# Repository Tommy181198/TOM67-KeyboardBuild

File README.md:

# TOM67-KeyboardBuild
 My First ever keyboard build

 MCU Schemantics:

 The rest of the Schemantics :

The Matrix :

The PCB Component placement before routing

Switch Matrix Routing (its a mess):

Crystal Route:

USB TYPE C Power Routing (I know its a mess) :

Finished Route

3D Render :

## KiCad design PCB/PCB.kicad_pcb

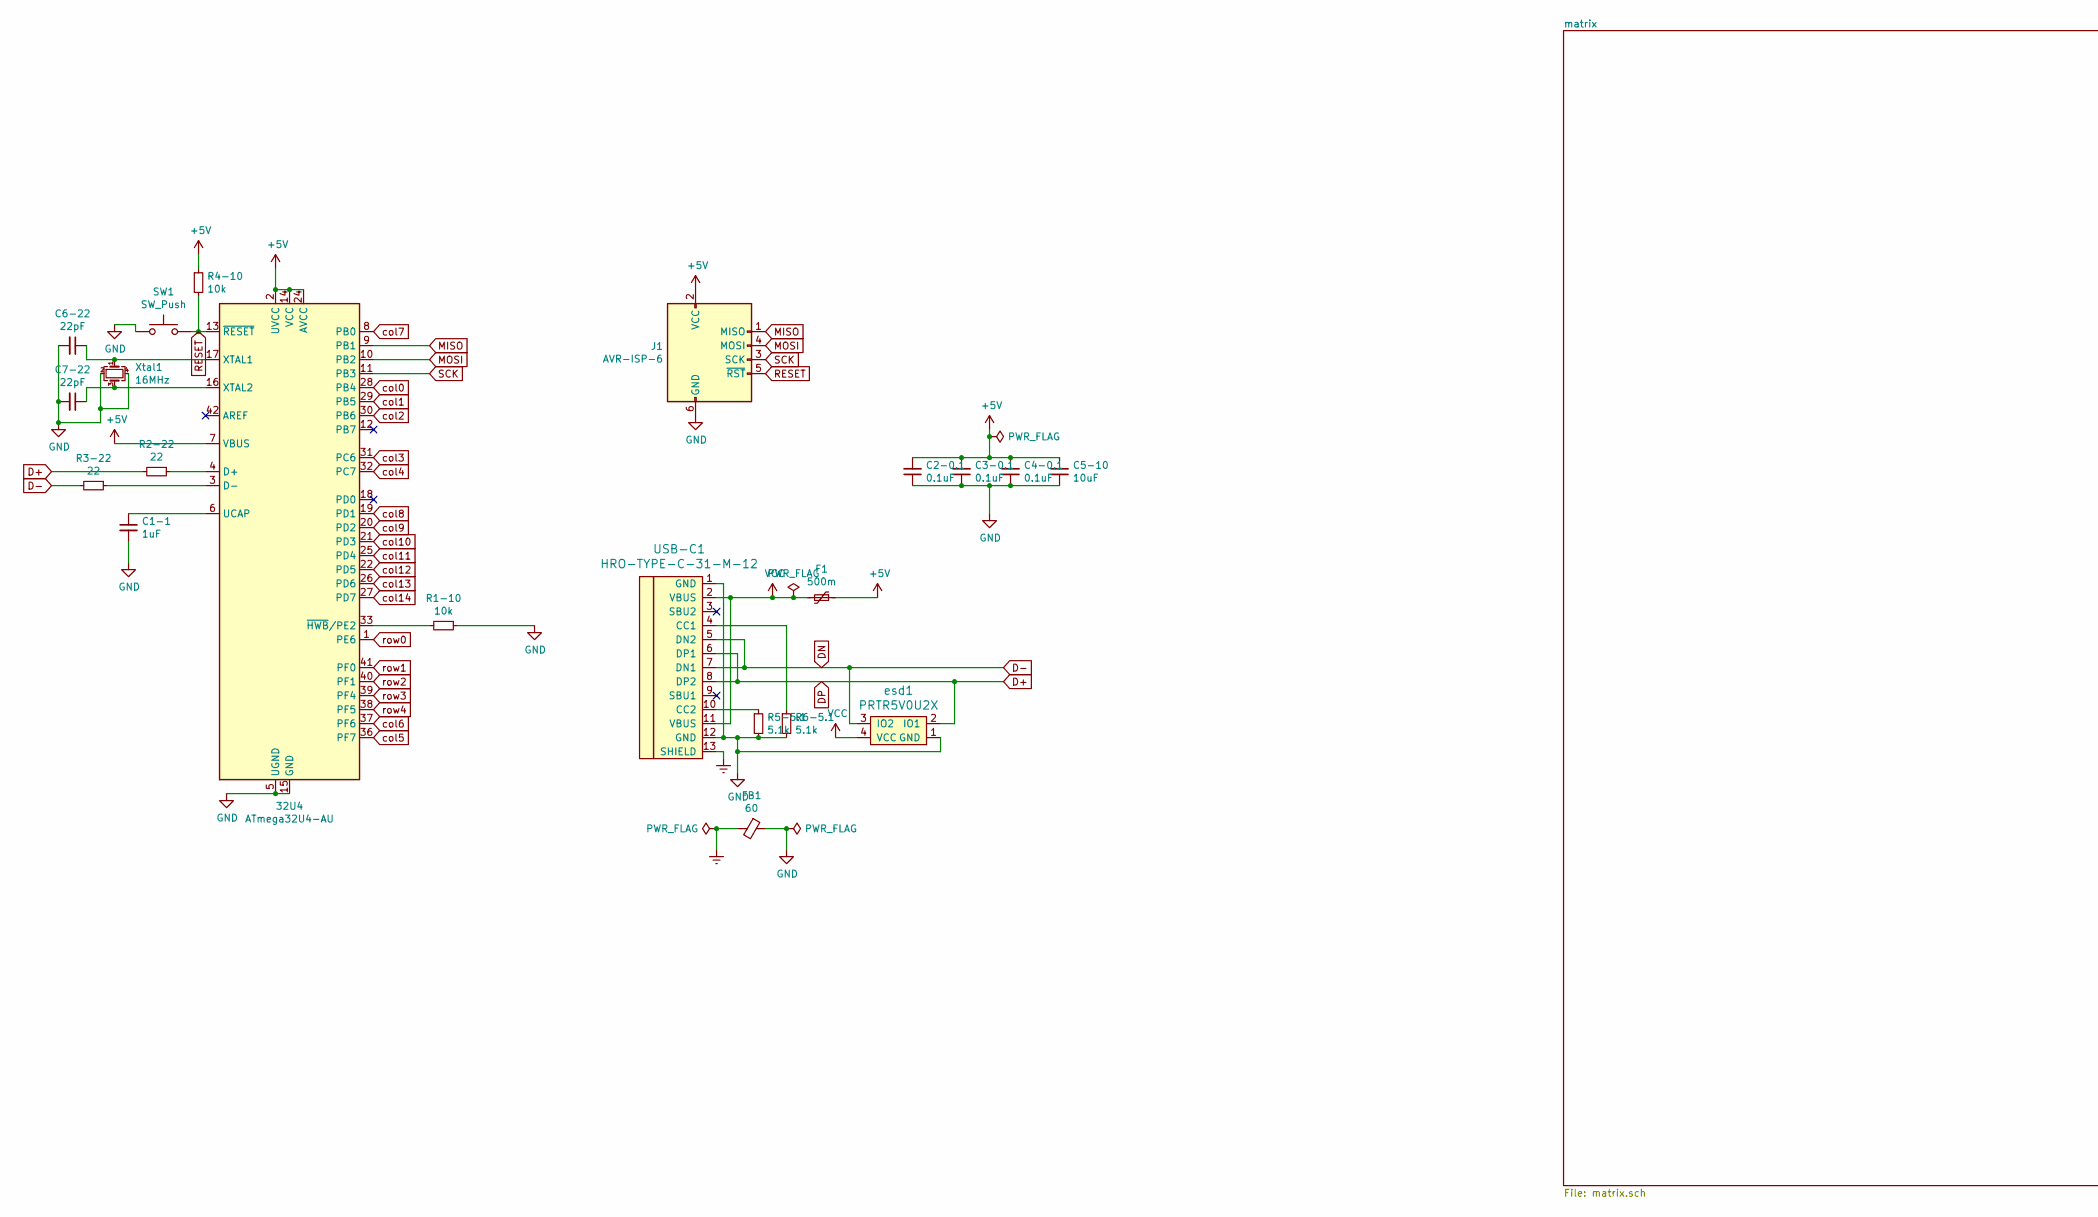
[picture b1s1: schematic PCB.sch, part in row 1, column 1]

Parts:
32U4: ATmega32U4-AU; TQFP-44_10x10mm_P0.8mm
C1-1: 1uF; C_0805_2012Metric_Pad1.18x1.45mm_HandSolder
C2-0.1, C3-0.1, C4-0.1: 0.1uF; C_0805_2012Metric_Pad1.18x1.45mm_HandSolder
C5-10: 10uF; C_0805_2012Metric_Pad1.18x1.45mm_HandSolder
C6-22, C7-22: 22pF; C_0805_2012Metric_Pad1.18x1.45mm_HandSolder
F1: 500m; Fuse_1206_3216Metric_Pad1.42x1.75mm_HandSolder
FB1: 60; L_0805_2012Metric_Pad1.05x1.20mm_HandSolder
J1: AVR-ISP-6; Reset_Pretty
R1-10, R4-10: 10k; R_0805_2012Metric_Pad1.20x1.40mm_HandSolder
R2-22, R3-22: 22; R_0805_2012Metric_Pad1.20x1.40mm_HandSolder
R5-5.1, R6-5.1: 5.1k; R_0805_2012Metric_Pad1.20x1.40mm_HandSolder
SW1: SW_Push; SW_SPST_TL3342
USB-C1: HRO-TYPE-C-31-M-12; HRO-TYPE-C-31-M-12-HandSoldering
Xtal1: 16MHz; Crystal_SMD_3225-4Pin_3.2x2.5mm
esd1: PRTR5V0U2X; SOT143B

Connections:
+5V: 32U4.2 (UVCC), 32U4.7 (VBUS), 32U4.14 (VCC), 32U4.24 (AVCC), 32U4.34 (VCC), 32U4.44 (AVCC), C2-0.1.2, C3-0.1.2, C4-0.1.2, C5-10.2, F1.1, J1.2 (VCC), R4-10.1
D+: R2-22.2, USB-C1.6 (DP1), USB-C1.8 (DP2), esd1.2 (IO1)
D-: R3-22.2, USB-C1.5 (DN2), USB-C1.7 (DN1), esd1.3 (IO2)
Earth: FB1.2, USB-C1.13 (SHIELD)
GND: 32U4.5 (UGND), 32U4.15 (GND), 32U4.23 (GND), 32U4.35 (GND), 32U4.43 (GND), C1-1.2, C2-0.1.1, C3-0.1.1, C4-0.1.1, C5-10.1, C6-22.2, C7-22.2, FB1.1, J1.6 (GND), R1-10.1, R5-5.1.2, R6-5.1.2, SW1.1, USB-C1.1 (GND), USB-C1.12 (GND), Xtal1.2, Xtal1.4, esd1.1 (GND)
MISO: 32U4.9 (PB1), J1.1 (MISO)
MOSI: 32U4.10 (PB2), J1.4 (MOSI)
unnamed: 32U4.3 (D-), R3-22.1
unnamed: 32U4.4 (D+), R2-22.1
unnamed: 32U4.6 (UCAP), C1-1.1
unnamed: 32U4.16 (XTAL2), C7-22.1, Xtal1.3
unnamed: 32U4.17 (XTAL1), C6-22.1, Xtal1.1
unnamed: 32U4.33 (~HWB~/PE2), R1-10.2
unnamed: R5-5.1.1, USB-C1.10 (CC2)
unnamed: R6-5.1.1, USB-C1.4 (CC1)
RESET: 32U4.13 (~RESET), J1.5 (~RST), R4-10.2, SW1.2
SCK: 32U4.11 (PB3), J1.3 (SCK)
VCC: F1.2, USB-C1.2 (VBUS), USB-C1.11 (VBUS), esd1.4 (VCC)
col0: 32U4.28 (PB4); also elsewhere on the board
col1: 32U4.29 (PB5); also elsewhere on the board
col2: 32U4.30 (PB6); also elsewhere on the board
col3: 32U4.31 (PC6); also elsewhere on the board
col4: 32U4.32 (PC7); also elsewhere on the board
col5: 32U4.36 (PF7); also elsewhere on the board
col6: 32U4.37 (PF6); also elsewhere on the board
col7: 32U4.8 (PB0); also elsewhere on the board
col8: 32U4.19 (PD1); also elsewhere on the board
col9: 32U4.20 (PD2); also elsewhere on the board
col10: 32U4.21 (PD3); also elsewhere on the board
col11: 32U4.25 (PD4); also elsewhere on the board
col12: 32U4.22 (PD5); also elsewhere on the board
col13: 32U4.26 (PD6); also elsewhere on the board
col14: 32U4.27 (PD7); also elsewhere on the board
row0: 32U4.1 (PE6); also elsewhere on the board
row1: 32U4.41 (PF0); also elsewhere on the board
row2: 32U4.40 (PF1); also elsewhere on the board
row3: 32U4.39 (PF4); also elsewhere on the board
row4: 32U4.38 (PF5); also elsewhere on the board

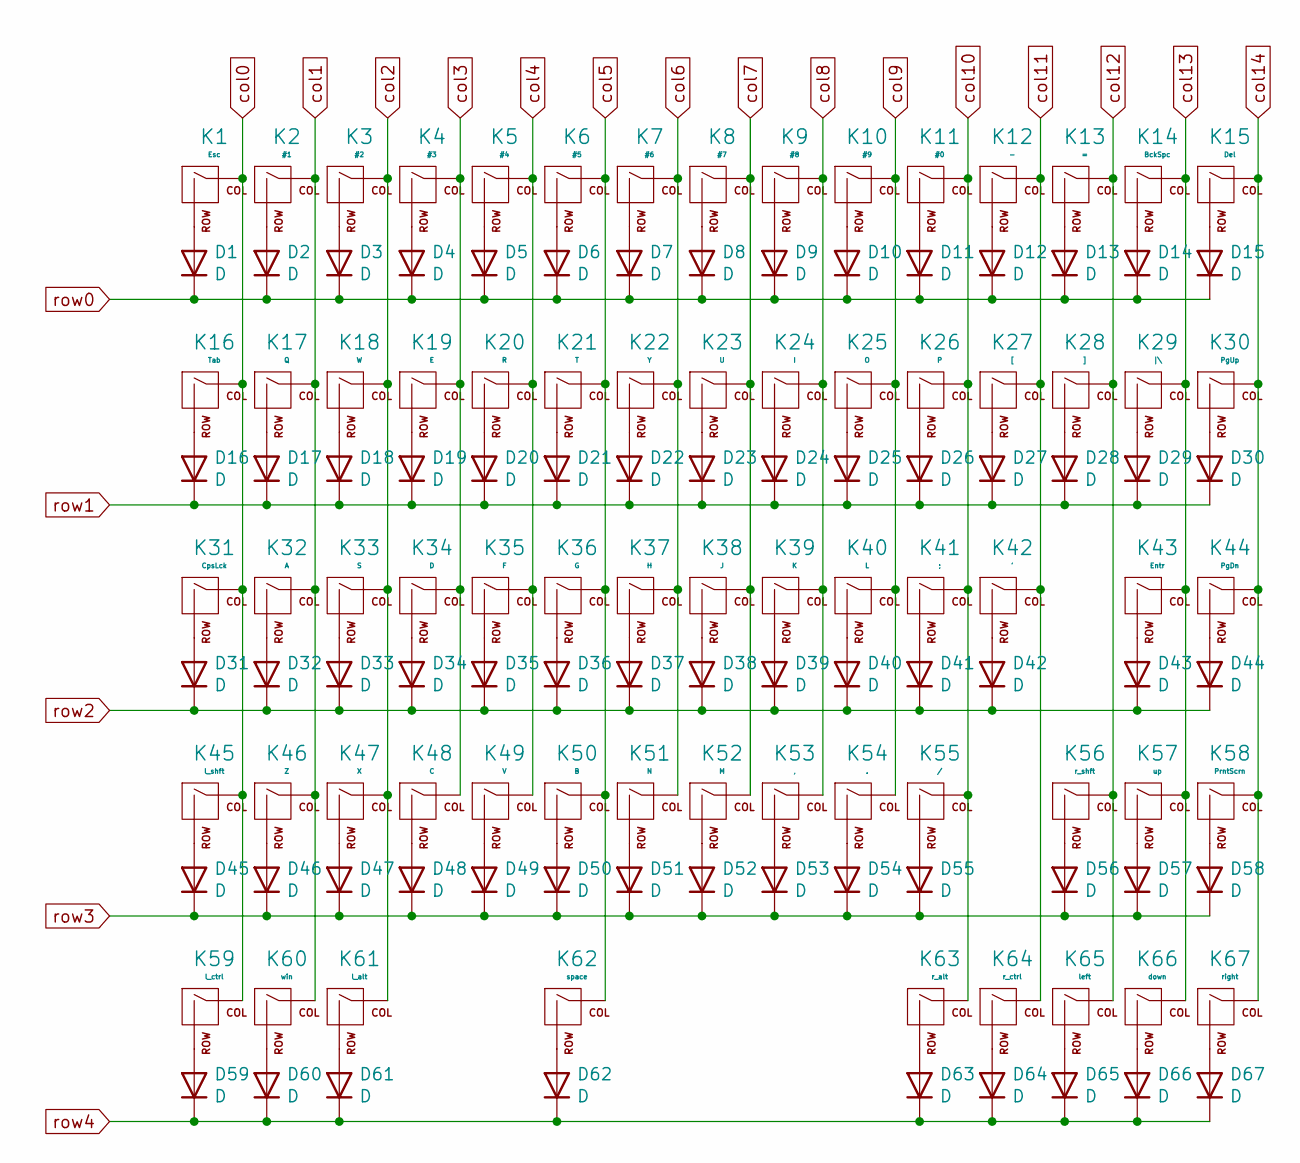
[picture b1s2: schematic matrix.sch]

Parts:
D1, D2, D3, D4, D5, D6, D7, D8, D9, D10, D11, D12, D13, D14, D15, D16, D17, D18, D19, D20, D21, D22, D23, D24, D25, D26, D27, D28, D29, D30, D31, D32, D33, D34, D35, D36, D37, D38, D39, D40, D41, D42, D43, D44, D45, D46, D47, D48, D49, D50, D51, D52, D53, D54, D55, D56, D57, D58, D59, D60, D61, D62, D63, D64, D65, D66, D67: D; D_SOD-123
K1: Esc; MXOnly-1U-Hotswap
K2: #1; MXOnly-1U-Hotswap
K3: #2; MXOnly-1U-Hotswap
K4: #3; MXOnly-1U-Hotswap
K5: #4; MXOnly-1U-Hotswap
K6: #5; MXOnly-1U-Hotswap
K7: #6; MXOnly-1U-Hotswap
K8: #7; MXOnly-1U-Hotswap
K9: #8; MXOnly-1U-Hotswap
K10: #9; MXOnly-1U-Hotswap
K11: #0; MXOnly-1U-Hotswap
K12: -; MXOnly-1U-Hotswap
K13: =; MXOnly-1U-Hotswap
K14: BckSpc; MXOnly-2U-Hotswap
K15: Del; MXOnly-1U-Hotswap
K16: Tab; MXOnly-1.5U-Hotswap
K17: Q; MXOnly-1U-Hotswap
K18: W; MXOnly-1U-Hotswap
K19: E; MXOnly-1U-Hotswap
K20: R; MXOnly-1U-Hotswap
K21: T; MXOnly-1U-Hotswap
K22: Y; MXOnly-1U-Hotswap
K23: U; MXOnly-1U-Hotswap
K24: I; MXOnly-1U-Hotswap
K25: O; MXOnly-1U-Hotswap
K26: P; MXOnly-1U-Hotswap
K27: [; MXOnly-1U-Hotswap
K28: ]; MXOnly-1U-Hotswap
K29: |\\; MXOnly-1.5U-Hotswap
K30: PgUp; MXOnly-1U-Hotswap
K31: CpsLck; MXOnly-1.75U-Hotswap
K32: A; MXOnly-1U-Hotswap
K33: S; MXOnly-1U-Hotswap
K34: D; MXOnly-1U-Hotswap
K35: F; MXOnly-1U-Hotswap
K36: G; MXOnly-1U-Hotswap
K37: H; MXOnly-1U-Hotswap
K38: J; MXOnly-1U-Hotswap
K39: K; MXOnly-1U-Hotswap
K40: L; MXOnly-1U-Hotswap
K41: ;; MXOnly-1U-Hotswap
K42: '; MXOnly-1U-Hotswap
K43: Entr; MXOnly-2.25U-Hotswap
K44: PgDn; MXOnly-1U-Hotswap
K45: l_shft; MXOnly-2.25U-Hotswap
K46: Z; MXOnly-1U-Hotswap
K47: X; MXOnly-1U-Hotswap
K48: C; MXOnly-1U-Hotswap
K49: V; MXOnly-1U-Hotswap
K50: B; MXOnly-1U-Hotswap
K51: N; MXOnly-1U-Hotswap
K52: M; MXOnly-1U-Hotswap
K53: ,; MXOnly-1U-Hotswap
K54: .; MXOnly-1U-Hotswap
K55: /; MXOnly-1U-Hotswap
K56: r_shft; MXOnly-1.75U-Hotswap
K57: up; MXOnly-1U-Hotswap
K58: PrntScrn; MXOnly-1U-Hotswap
K59: l_ctrl; MXOnly-1.25U-Hotswap
K60: win; MXOnly-1.25U-Hotswap
K61: l_alt; MXOnly-1.25U-Hotswap
K62: space; MXOnly-6.25U-Hotswap-ReversedStabilizers
K63: r_alt; MXOnly-1.25U-Hotswap
K64: r_ctrl; MXOnly-1.25U-Hotswap
K65: left; MXOnly-1U-Hotswap
K66: down; MXOnly-1U-Hotswap
K67: right; MXOnly-1U-Hotswap

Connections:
unnamed: D1.1 (A), K1.2 (ROW)
unnamed: D2.1 (A), K2.2 (ROW)
unnamed: D3.1 (A), K3.2 (ROW)
unnamed: D4.1 (A), K4.2 (ROW)
unnamed: D5.1 (A), K5.2 (ROW)
unnamed: D6.1 (A), K6.2 (ROW)
unnamed: D7.1 (A), K7.2 (ROW)
unnamed: D8.1 (A), K8.2 (ROW)
unnamed: D9.1 (A), K9.2 (ROW)
unnamed: D10.1 (A), K10.2 (ROW)
unnamed: D11.1 (A), K11.2 (ROW)
unnamed: D12.1 (A), K12.2 (ROW)
unnamed: D13.1 (A), K13.2 (ROW)
unnamed: D14.1 (A), K14.2 (ROW)
unnamed: D15.1 (A), K15.2 (ROW)
unnamed: D16.1 (A), K16.2 (ROW)
unnamed: D17.1 (A), K17.2 (ROW)
unnamed: D18.1 (A), K18.2 (ROW)
unnamed: D19.1 (A), K19.2 (ROW)
unnamed: D20.1 (A), K20.2 (ROW)
unnamed: D21.1 (A), K21.2 (ROW)
unnamed: D22.1 (A), K22.2 (ROW)
unnamed: D23.1 (A), K23.2 (ROW)
unnamed: D24.1 (A), K24.2 (ROW)
unnamed: D25.1 (A), K25.2 (ROW)
unnamed: D26.1 (A), K26.2 (ROW)
unnamed: D27.1 (A), K27.2 (ROW)
unnamed: D28.1 (A), K28.2 (ROW)
unnamed: D29.1 (A), K29.2 (ROW)
unnamed: D30.1 (A), K30.2 (ROW)
unnamed: D31.1 (A), K31.2 (ROW)
unnamed: D32.1 (A), K32.2 (ROW)
unnamed: D33.1 (A), K33.2 (ROW)
unnamed: D34.1 (A), K34.2 (ROW)
unnamed: D35.1 (A), K35.2 (ROW)
unnamed: D36.1 (A), K36.2 (ROW)
unnamed: D37.1 (A), K37.2 (ROW)
unnamed: D38.1 (A), K38.2 (ROW)
unnamed: D39.1 (A), K39.2 (ROW)
unnamed: D40.1 (A), K40.2 (ROW)
unnamed: D41.1 (A), K41.2 (ROW)
unnamed: D42.1 (A), K42.2 (ROW)
unnamed: D43.1 (A), K43.2 (ROW)
unnamed: D44.1 (A), K44.2 (ROW)
unnamed: D45.1 (A), K45.2 (ROW)
unnamed: D46.1 (A), K46.2 (ROW)
unnamed: D47.1 (A), K47.2 (ROW)
unnamed: D48.1 (A), K48.2 (ROW)
unnamed: D49.1 (A), K49.2 (ROW)
unnamed: D50.1 (A), K50.2 (ROW)
unnamed: D51.1 (A), K51.2 (ROW)
unnamed: D52.1 (A), K52.2 (ROW)
unnamed: D53.1 (A), K53.2 (ROW)
unnamed: D54.1 (A), K54.2 (ROW)
unnamed: D55.1 (A), K55.2 (ROW)
unnamed: D56.1 (A), K56.2 (ROW)
unnamed: D57.1 (A), K57.2 (ROW)
unnamed: D58.1 (A), K58.2 (ROW)
unnamed: D59.1 (A), K59.2 (ROW)
unnamed: D60.1 (A), K60.2 (ROW)
unnamed: D61.1 (A), K61.2 (ROW)
unnamed: D62.1 (A), K62.2 (ROW)
unnamed: D63.1 (A), K63.2 (ROW)
unnamed: D64.1 (A), K64.2 (ROW)
unnamed: D65.1 (A), K65.2 (ROW)
unnamed: D66.1 (A), K66.2 (ROW)
unnamed: D67.1 (A), K67.2 (ROW)
col0: K1.1 (COL), K16.1 (COL), K31.1 (COL), K45.1 (COL), K59.1 (COL); also elsewhere on the board
col1: K2.1 (COL), K17.1 (COL), K32.1 (COL), K46.1 (COL), K60.1 (COL); also elsewhere on the board
col2: K3.1 (COL), K18.1 (COL), K33.1 (COL), K47.1 (COL), K61.1 (COL); also elsewhere on the board
col3: K4.1 (COL), K19.1 (COL), K34.1 (COL), K48.1 (COL); also elsewhere on the board
col4: K5.1 (COL), K20.1 (COL), K35.1 (COL), K49.1 (COL); also elsewhere on the board
col5: K6.1 (COL), K21.1 (COL), K36.1 (COL), K50.1 (COL), K62.1 (COL); also elsewhere on the board
col6: K7.1 (COL), K22.1 (COL), K37.1 (COL), K51.1 (COL); also elsewhere on the board
col7: K8.1 (COL), K23.1 (COL), K38.1 (COL), K52.1 (COL); also elsewhere on the board
col8: K9.1 (COL), K24.1 (COL), K39.1 (COL), K53.1 (COL); also elsewhere on the board
col9: K10.1 (COL), K25.1 (COL), K40.1 (COL), K54.1 (COL); also elsewhere on the board
col10: K11.1 (COL), K26.1 (COL), K41.1 (COL), K55.1 (COL), K63.1 (COL); also elsewhere on the board
col11: K12.1 (COL), K27.1 (COL), K42.1 (COL), K64.1 (COL); also elsewhere on the board
col12: K13.1 (COL), K28.1 (COL), K56.1 (COL), K65.1 (COL); also elsewhere on the board
col13: K14.1 (COL), K29.1 (COL), K43.1 (COL), K57.1 (COL), K66.1 (COL); also elsewhere on the board
col14: K15.1 (COL), K30.1 (COL), K44.1 (COL), K58.1 (COL), K67.1 (COL); also elsewhere on the board
row0: D1.2 (K), D2.2 (K), D3.2 (K), D4.2 (K), D5.2 (K), D6.2 (K), D7.2 (K), D8.2 (K), D9.2 (K), D10.2 (K), D11.2 (K), D12.2 (K), D13.2 (K), D14.2 (K), D15.2 (K); also elsewhere on the board
row1: D16.2 (K), D17.2 (K), D18.2 (K), D19.2 (K), D20.2 (K), D21.2 (K), D22.2 (K), D23.2 (K), D24.2 (K), D25.2 (K), D26.2 (K), D27.2 (K), D28.2 (K), D29.2 (K), D30.2 (K); also elsewhere on the board
row2: D31.2 (K), D32.2 (K), D33.2 (K), D34.2 (K), D35.2 (K), D36.2 (K), D37.2 (K), D38.2 (K), D39.2 (K), D40.2 (K), D41.2 (K), D42.2 (K), D43.2 (K), D44.2 (K); also elsewhere on the board
row3: D45.2 (K), D46.2 (K), D47.2 (K), D48.2 (K), D49.2 (K), D50.2 (K), D51.2 (K), D52.2 (K), D53.2 (K), D54.2 (K), D55.2 (K), D56.2 (K), D57.2 (K), D58.2 (K); also elsewhere on the board
row4: D59.2 (K), D60.2 (K), D61.2 (K), D62.2 (K), D63.2 (K), D64.2 (K), D65.2 (K), D66.2 (K), D67.2 (K); also elsewhere on the board

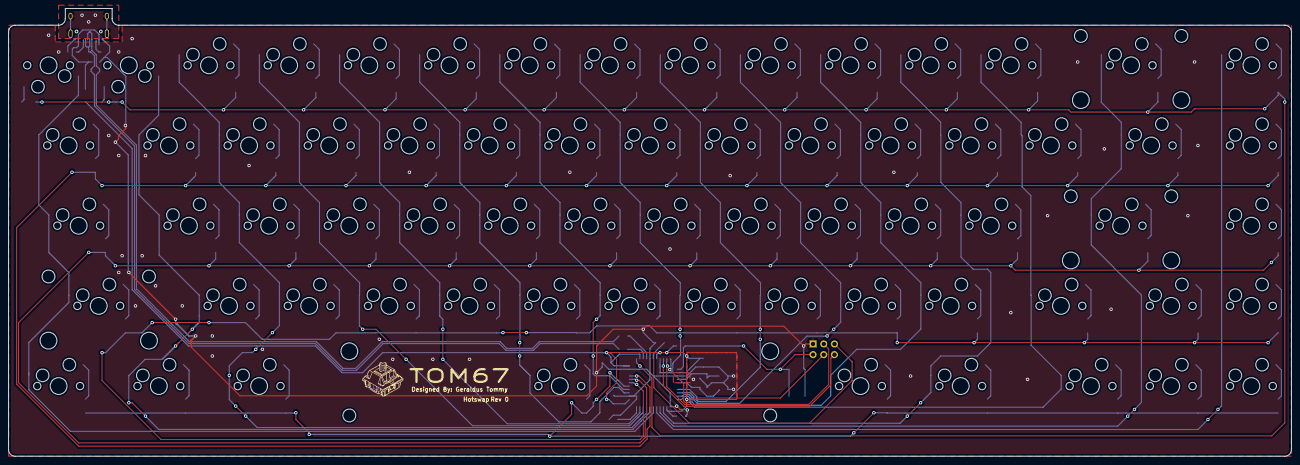
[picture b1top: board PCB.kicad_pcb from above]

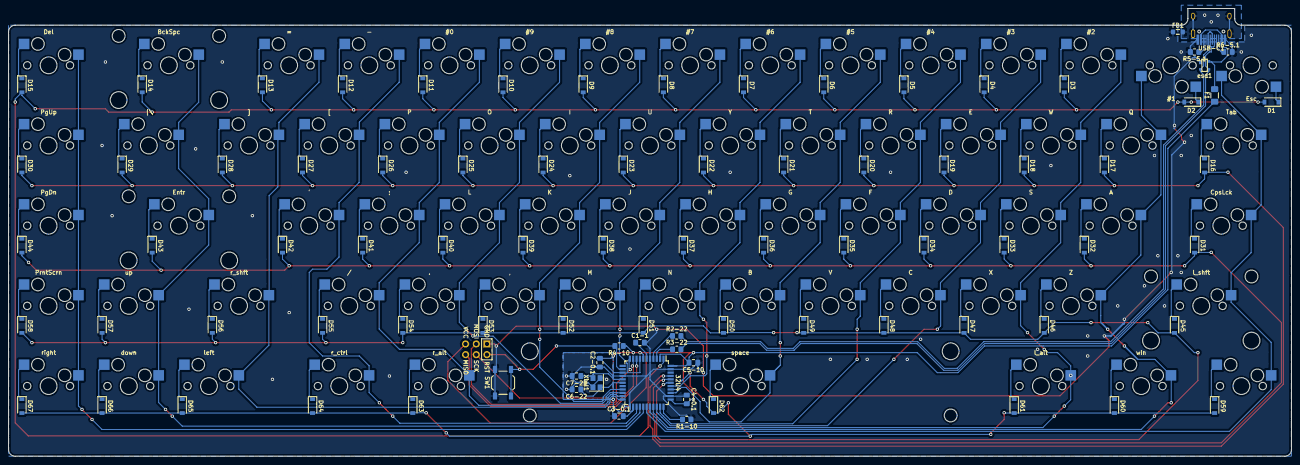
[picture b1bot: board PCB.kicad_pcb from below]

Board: 2 copper layers, 304.8 x 106.4 mm, 155 parts (88 on the bottom side), 105 nets.

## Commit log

2022-01-20 PCB init
    PCB init
2022-01-20 Add submodules kicad.lib
2022-01-20 FootPrints
2022-01-20 usb c lib
2022-01-20 add usb c footprints
2022-01-20 Keyboard Matrix
2022-01-20 Schemantics
2022-01-20 import schemantics to pcb
2022-01-21 pcb alignment
2022-01-21 switch matrix routing
2022-01-22 PCB Done
